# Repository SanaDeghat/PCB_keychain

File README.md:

# PCB_keychain
I wanna try making a cute PCB keychain 
So i finished it!! Super cute and really simple admittedly. 
You might be like HMMMM sana how did this take you 2 HOURS??? well im not veruy smart it turns out also i tried a bunch of tnew stuff 
First PCB i ever made without any tutorial, I also learned how to chance DRC and add my own footprints and efit footprints :D 

3d View:

PCB:

Schematics:

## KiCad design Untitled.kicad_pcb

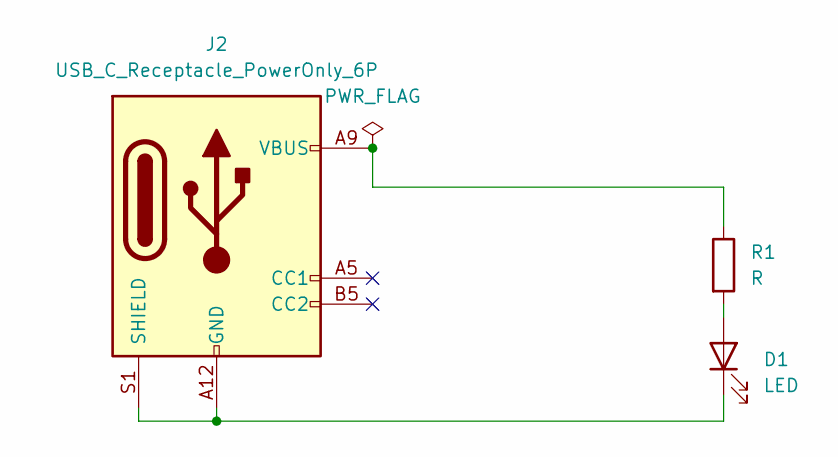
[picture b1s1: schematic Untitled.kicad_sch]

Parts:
D1: LED; LED_RGB_1210
J2: USB_C_Receptacle_PowerOnly_6P; USB_C_Plug_smaller
R1: R; R_01005_0402Metric

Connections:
unnamed: D1.2 (A), R1.2
unnamed: D1.1 (K), J2.A12 (GND), J2.B12 (GND), J2.S1 (SHIELD)
unnamed: J2.A9 (VBUS), J2.B9 (VBUS), R1.1

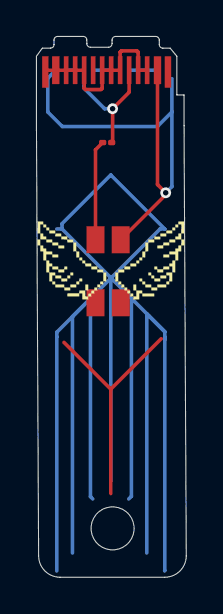
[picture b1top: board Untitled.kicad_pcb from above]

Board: 2 copper layers, 8.3 x 30.0 mm, 3 parts (0 on the bottom side), 3 nets.

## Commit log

2026-03-31 I soent the last 1 hour trying t ofigure out how to import PCBs
2026-03-31 FINSIHEDDD
2026-03-31 Update README with images and project details
    Added images of the 3D view, PCB, and schematics to README.
2026-03-31 Update README with PCB keychain images
    Added images of the PCB keychain, 3D view, and schematics.
